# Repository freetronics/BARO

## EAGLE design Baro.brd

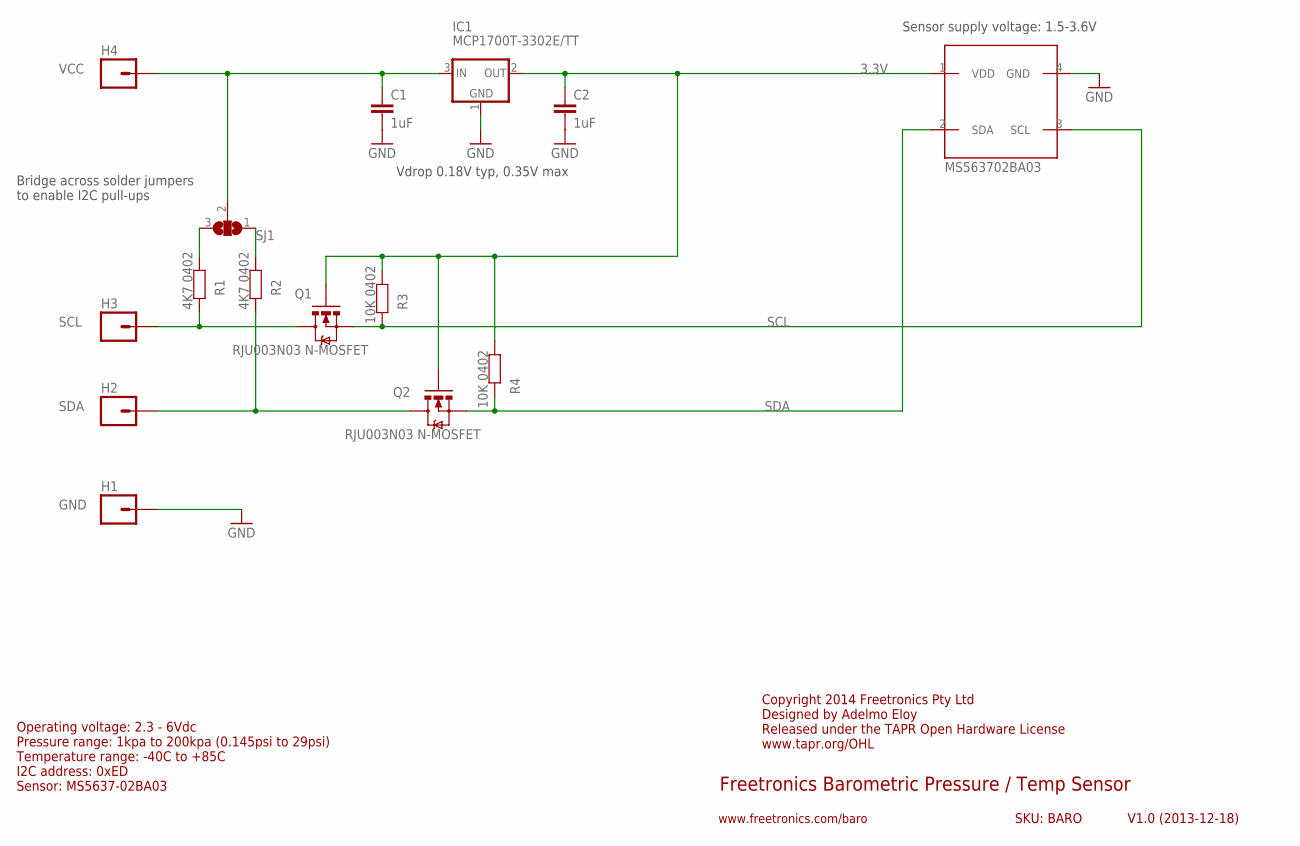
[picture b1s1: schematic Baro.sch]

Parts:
C1, C2: 1uF; 0603
H1: GND; 1X01
H2: SDA; 1X01
H3: SCL; 1X01
H4: VCC; 1X01
IC1: MCP1700T-3302E/TT; SOT23-3
IC2: MS563702BA03; MS5637
Q1, Q2: RJU003N03 N-MOSFET; SOT32-3
R1, R2: 4K7 0402; 0402
R3, R4: 10K 0402; 0402
SJ1: SJ2W; SJ_2

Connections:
3.3V: C2.1, IC1.2 (OUT), IC2.1 (VDD), Q1.1 (G), Q2.1 (G), R3.2, R4.2
GND: C1.2, C2.2, H1.1, IC1.1 (GND), IC2.4 (GND)
unnamed: IC2.3 (SCL), Q1.2 (S), R3.1
unnamed: C1.1, H4.1, IC1.3 (IN), SJ1.2
unnamed: IC2.2 (SDA), Q2.2 (S), R4.1
unnamed: R1.2, SJ1.3
unnamed: R2.2, SJ1.1
SCL: H3.1, Q1.3 (D), R1.1
SDA: H2.1, Q2.3 (D), R2.1

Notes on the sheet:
Freetronics Barometric Pressure / Temp Sensor
V1.0 (2013-12-18)
www.freetronics.com/baro
SKU: BARO
Sensor supply voltage: 1.5-3.6V
Bridge across solder jumpers to enable I2C pull-ups
Vdrop 0.18V typ, 0.35V max
Copyright 2014 Freetronics Pty Ltd Designed by Adelmo Eloy Released under the TAPR Open Hardware License www.tapr.org/OHL
Operating voltage: 2.3 - 6Vdc Pressure range: 1kpa to 200kpa (0.145psi to 29psi) Temperature range: -40C to +85C I2C address: 0xED Sensor: MS5637-02BA03

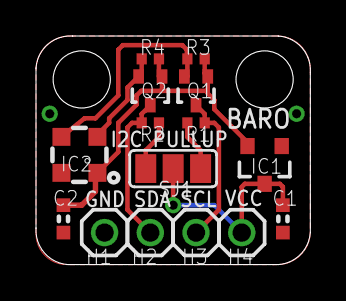
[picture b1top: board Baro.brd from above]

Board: 2 copper layers, 15.2 x 12.7 mm, 15 parts (0 on the bottom side), 9 nets.

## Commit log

2013-12-17 Initial project.
2013-12-18 Volt. regulator and FETs added.
2014-01-21 Noted Adelmo Eloy as the designer Added license info to schematic Relocated decoupling cap to near sensor Improved ground connection to regulator Added notes to schematic about operating ranges Chang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
2014-01-21 Fixed revision date
2014-01-21 Approved ERC errors
2014-06-20 Bridged I2C pullup jumpers Shortened URL

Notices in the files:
Baro.brd:
(c) 2014 Freetronics
parts and their libraries:
freetronics-original: Licensing: CC v3.0 Share-Alike You are welcome to use this library for commercial purposes.
